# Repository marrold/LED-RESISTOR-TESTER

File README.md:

# LED Resistor Tester

A PCB for testing LED brightness with various LEDs to get an equal brightness across different LEDs.

**Note:** It's currently untested

## License

- This project is licensed under the MIT license

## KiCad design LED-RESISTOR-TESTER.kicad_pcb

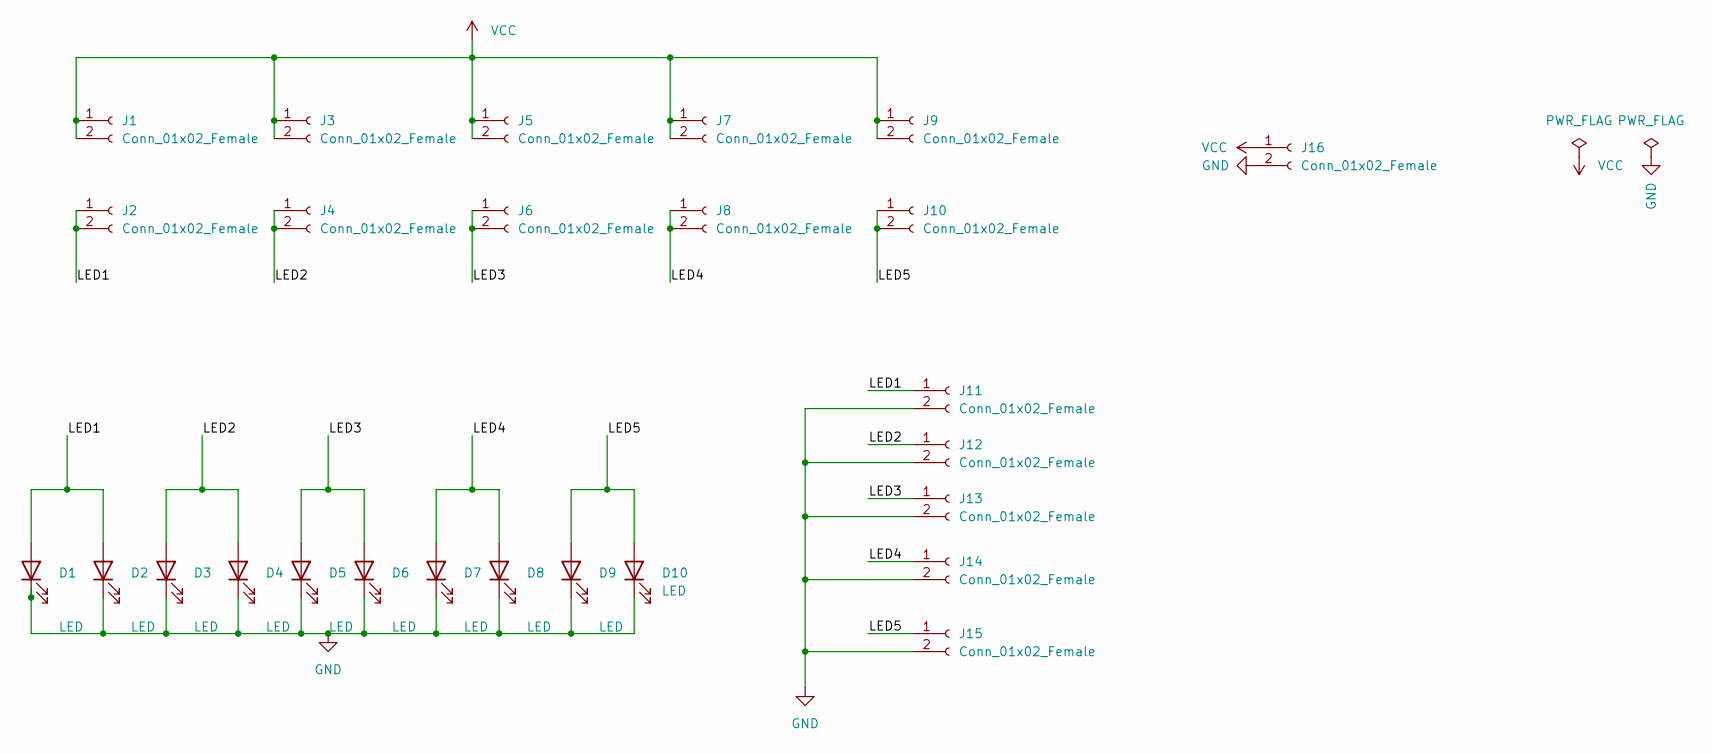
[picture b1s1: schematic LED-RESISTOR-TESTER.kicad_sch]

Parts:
D1, D3, D5, D7, D9: LED; LED_0805_2012Metric_Pad1.15x1.40mm_HandSolder
D2, D4, D6, D8, D10: LED; LED_0603_1608Metric_Pad1.05x0.95mm_HandSolder
J1, J2, J3, J4, J5, J6, J7, J8, J9, J10, J11, J12, J13, J14, J15, J16: Conn_01x02_Female; PinSocket_1x02_P2.54mm_Vertical

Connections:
/LED1: D1.2 (A), D2.2 (A), J2.1, J2.2, J11.1
/LED2: D3.2 (A), D4.2 (A), J4.1, J4.2, J12.1
/LED3: D5.2 (A), D6.2 (A), J6.1, J6.2, J13.1
/LED4: D7.2 (A), D8.2 (A), J8.1, J8.2, J14.1
/LED5: D9.2 (A), D10.2 (A), J10.1, J10.2, J15.1
GND: D1.1 (K), D2.1 (K), D3.1 (K), D4.1 (K), D5.1 (K), D6.1 (K), D7.1 (K), D8.1 (K), D9.1 (K), D10.1 (K), J11.2, J12.2, J13.2, J14.2, J15.2, J16.2
VCC: J1.1, J1.2, J3.1, J3.2, J5.1, J5.2, J7.1, J7.2, J9.1, J9.2, J16.1

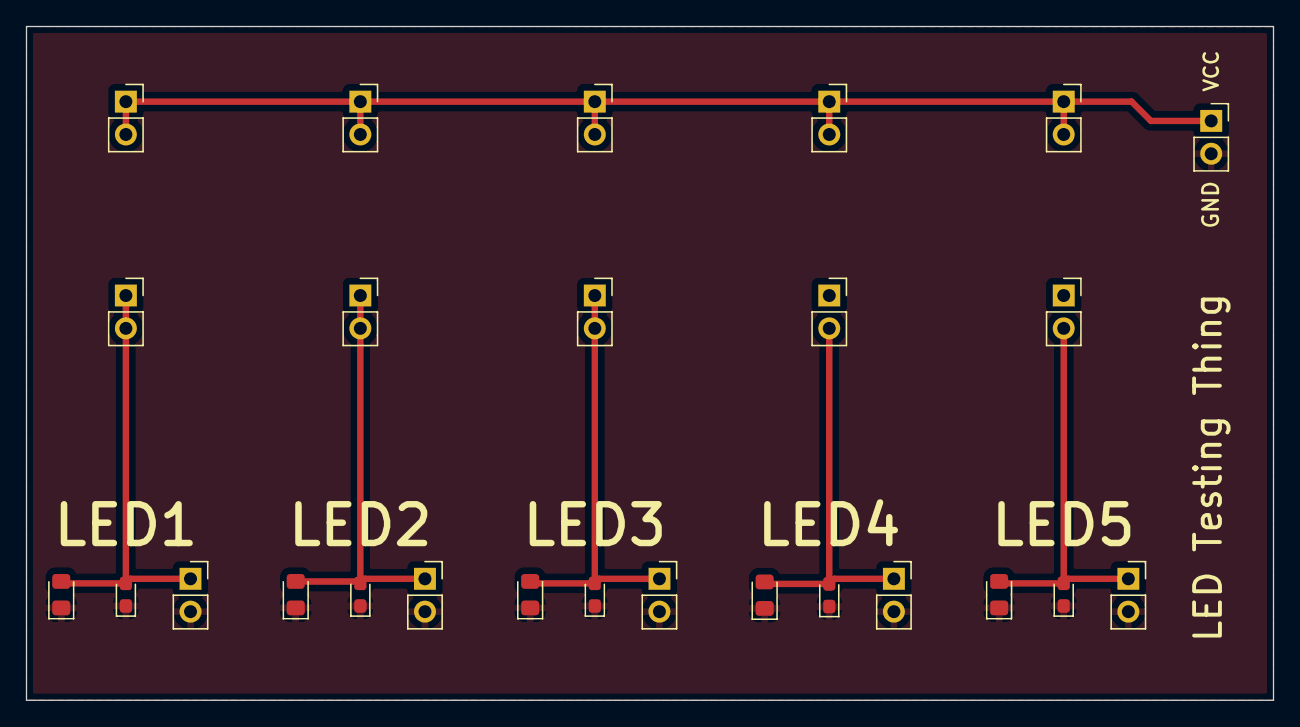
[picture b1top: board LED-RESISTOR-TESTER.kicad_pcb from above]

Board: 2 copper layers, 96.5 x 52.1 mm, 26 parts (0 on the bottom side), 7 nets.

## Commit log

2024-01-05 init
2024-01-05 Remove notes panel
